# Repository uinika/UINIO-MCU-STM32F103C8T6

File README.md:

# UINIO-MCU-STM32F103C8T6 核心板

[**UINIO-MCU-STM32F103C8T6**](https://gitee.com/uinika/UINIO-MCU-STM32F103C8T6) 是一款基于 [**意法半导体**](https://www.st.com/zh/microcontrollers-microprocessors/stm32-32-bit-arm-cortex-mcus.html) **LQFP48** 封装的 **STM3232F103C8T6** 微控制器的核心板电路设计，该微控制器基于 **ARM Cortex-M3** 内核架构，主频可以达到 `72MHz`，片上载有 `64KB` 容量的 Flash 存储器和 `20Kbytes` 的 SRAM 存储器，并且拥有 3 组 **USART** 和 2 组 **I²C** 接口，以及 2 组 **SPI** 接口与 `USB2.0` 全速控制器、12 位分辨率的 `ADC/DAC` 转换器，整体上属于外设资源比较完善的高性价比主控芯片产品。

## 设计概要

1. 引出了意法半导体 **STM32F103C8T6** 型微控制器上面的全部 GPIO 引脚资源；
2. 单独提供有四线制的 **SWD** 下载接口，便于快速与 [UINIO-DAP-Link](http://uinio.com/Project/UINIO-DAP-Link) 建立连接；
3. 分别使用了 `8MHz` 与 `32.768KHz` 两枚贴片晶振作为系统外部时钟与实时时钟；
4. 板载 **BOOT0** 和 **BOOT1** 两枚启动配置按钮，以及一枚 **NRST** 复位按钮；
5. 模拟电源引脚 `VDDA` 使用了对 `100Mhz` 高频杂散信号存在 `1KΩ` 阻抗的**磁珠**进行单点接地；

## 启动配置

**UINIO-MCU-STM32F103C8T6** 通过板载的 `BOOT0` 和 `BOOT1` 两枚按钮来配置启动方式，默认情况下是从片上的 Flash 闪存进行启动，具体的配置信息可以参见下表：

| BOOT0 | BOOT1 | 启动方式                 |
| :---: | :---: | :----------------------- |
|  `0`  |  `X`  | 片上 Flash 闪存          |
|  `1`  |  `0`  | 系统存储器/ISP           |
|  `1`  |  `1`  | 片上 SRAM 静态随机存储器 |

## 参考技术文档

[UinIO.com 电子技术实验室](http://uinio.com/) 为 UINIO-MCU-STM32F103C8T6 开源项目提供了如下一系列技术参考资料：

1. [《意法半导体 STM32F103C8T6 标准库典型实例》](http://uinio.com/Embedded/STM32F103/)
2. [《ARM 调试工具 UINIO-DAP-Link 应用详解》](http://uinio.com/Project/UINIO-DAP-Link/)
3. [《BOM 交互式物料清单与 PCB 布线在线预览》](http://uinio.com/archives/BOM/UINIO-MCU-STM32F103C8T6.html)

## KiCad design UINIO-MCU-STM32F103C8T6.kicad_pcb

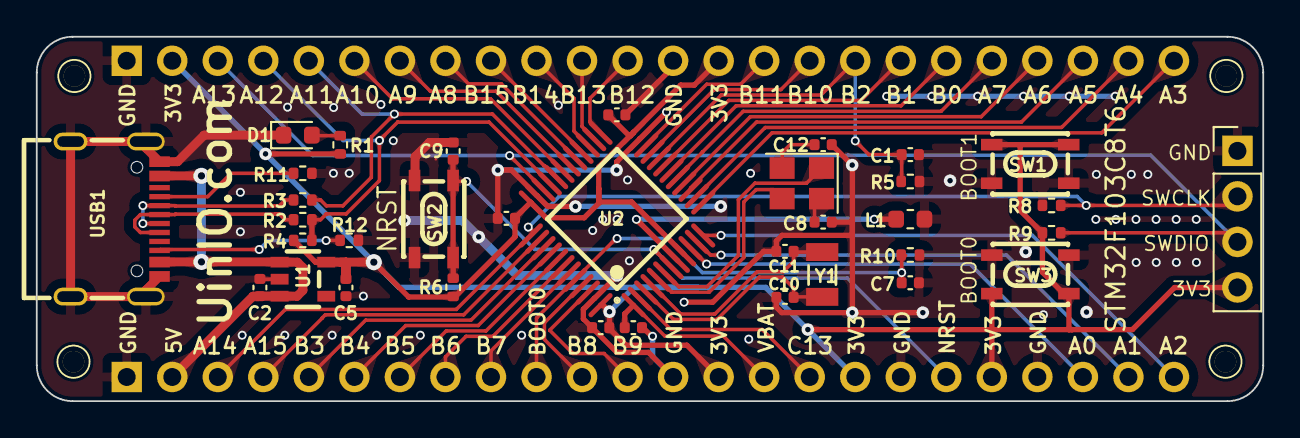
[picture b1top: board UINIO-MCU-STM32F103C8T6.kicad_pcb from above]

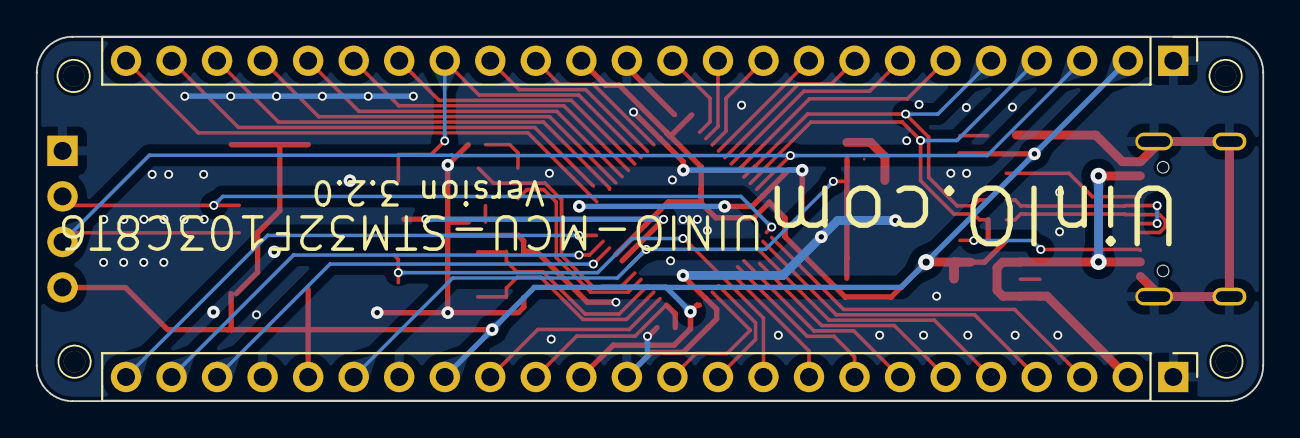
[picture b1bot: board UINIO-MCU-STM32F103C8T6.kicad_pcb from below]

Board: 2 copper layers, 68.4 x 20.3 mm, 41 parts (2 on the bottom side), 51 nets.

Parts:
C1, C3, C4, C6, C7, C9, C13: 0.1uF; C_0402_1005Metric
C2, C5: 1uF; C_0402_1005Metric
C8, C12: 22pF; C_0402_1005Metric
C10, C11: 10pF; C_0402_1005Metric
D1: LED_Red; LED_0603_1608Metric
HOLE**: Hole-1mm
HOLE**#2, HOLE**#3, HOLE**#4: Hole-1mm
J1, J2: Conn_01x24_Pin; PinHeader_1x24_P2.54mm_Vertical
J3: Conn_01x04_Pin; PinHeader_1x04_P2.54mm_Vertical
L1: 1KΩ 100Mhz; L_0603_1608Metric
R1: 2K; R_0402_1005Metric
R2, R3: 50R; R_0402_1005Metric
R4: 1.5K; R_0402_1005Metric
R5, R6, R8, R9, R10: 10K; R_0402_1005Metric
R11, R12: 5.1K; R_0402_1005Metric
SW1: BOOT1; KEY-SMD_4P-L4.2-W3.4-P2.15-LS4.7
SW2: NRST; KEY-SMD_4P-L4.2-W3.4-P2.15-LS4.7
SW3: BOOT0; KEY-SMD_4P-L4.2-W3.4-P2.15-LS4.7
U1: ME6211C33M5G-N; SOT-23-5_L3.0-W1.7-P0.95-LS2.8-BR
U2: STM32F103C8T6; TQFP-48_L7.0-W7.0-P0.50-LS9.0-BL
USB1: USB_Type_C_16Pin; USB-C-SMD_TYPEC-304J-BCP16
Y1: 32.768KHz; CRYSTAL-FC135-32.768
Y2: 8MHz; Crystal_SMD_3225-4Pin_3.2x2.5mm

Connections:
/BOOT0: C7.2, J2.10, R10.1, U2.44 (BOOT0)
/NRST: C9.1, J2.19, R6.2, SW2.1, SW2.2, U2.7 (NRST)
/PA0: J2.22, U2.10 (PA0_WAKEUP)
/PA1: J2.23, U2.11 (PA1)
/PA2: J2.24, U2.12 (PA2)
/PA3: J1.24, U2.13 (PA3)
/PA4: J1.23, U2.14 (PA4)
/PA5: J1.22, U2.15 (PA5)
/PA6: J1.21, U2.16 (PA6)
/PA7: J1.20, U2.17 (PA7)
/PA8: J1.8, U2.29 (PA8)
/PA9: J1.7, U2.30 (PA9)
/PA10: J1.6, U2.31 (PA10)
/PA13/SWDIO: J1.3, J3.3, R9.1, U2.34 (PA13)
/PA14/SWCLK: J2.3, J3.2, R8.2, U2.37 (PA14)
/PA15: J2.4, U2.38 (PA15)
/PB0: J1.19, U2.18 (PB0)
/PB1: J1.18, U2.19 (PB1)
/PB2/BOOT1: C1.2, J1.17, R5.1, U2.20 (PB2)
/PB3: J2.5, U2.39 (PB3)
/PB4: J2.6, U2.40 (PB4)
/PB5: J2.7, U2.41 (PB5)
/PB6: J2.8, U2.42 (PB6)
/PB7: J2.9, U2.43 (PB7)
/PB8: J2.11, U2.45 (PB8)
/PB9: J2.12, U2.46 (PB9)
/PB10: J1.16, U2.21 (PB10)
/PB11: J1.15, U2.22 (PB11)
/PB12: J1.12, U2.25 (PB12)
/PB13: J1.11, U2.26 (PB13)
/PB14: J1.10, U2.27 (PB14)
/PB15: J1.9, U2.28 (PB15)
/PC13: J2.16, U2.2 (PC13_TAMPER_RTC)
/USB_Data+: R2.1, USB1.A6 (DP1), USB1.B6 (DP2)
/USB_Data-: R3.1, USB1.A7 (DN1), USB1.B7 (DN2)
/USB_PA+: J1.4, R2.2, R4.2, U2.33 (PA12)
/USB_PA-: J1.5, R3.2, U2.32 (PA11)
/VBAT: C13.2, J2.15, U2.1 (VBAT)
/VDD_3.3V: C3.2, C4.2, C5.2, C6.2, J1.2, J1.14, J2.14, J2.17, J2.20, J3.4, R1.2, R4.1, R6.1, R9.2, SW1.3, SW1.4, SW3.3, SW3.4, U1.5 (Vout), U2.9 (VDDA), U2.24 (VDD_1), U2.36 (VDD_2), U2.48 (VDD_3)
/VDD_5V: C2.2, J2.2, U1.1 (Vin), U1.3 (CE), USB1.A4B9 (VBUS), USB1.B4A9 (VBUS)
GND: C1.1, C2.1, C3.1, C4.1, C5.1, C6.1, C7.1, C8.1, C9.2, C10.1, C11.1, C12.1, C13.1, D1.1 (K), J1.1, J1.13, J2.1, J2.13, J2.18, J2.21, J3.1, L1.1, R5.2, R8.1, R10.2, R11.2, R12.2, SW1.1, SW1.2, SW2.3, SW2.4, SW3.1, SW3.2, U1.2 (Vss), U2.23 (VSS_1), U2.35 (VSS_2), U2.47 (VSS_3), USB1.13 (GND), USB1.14 (GND), USB1.15 (GND), USB1.16 (GND), USB1.A1B12 (GND), USB1.B1A12 (GND)
unnamed: C8.2, Y2.4
unnamed: C12.2, Y2.2
unnamed: D1.2 (A), R1.1
unnamed: C10.2, U2.3 (PC14_OSC32_IN), Y1.2 (GND)
unnamed: C11.2, U2.4 (PC15_OSC32_OUT), Y1.1
unnamed: U2.5 (PD0_OSC_IN), Y2.3
unnamed: U2.6 (PD1_OSC_OUT), Y2.1
unnamed: L1.2, U2.8 (VSSA)
unnamed: R11.1, USB1.A5 (CC1)
unnamed: R12.1, USB1.B5 (CC2)

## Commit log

2024-02-04 Initialization project.
2024-02-04 Add reference documents.
2024-02-05 Complete wiring.
2024-02-05 Finish PCB layout.
2024-02-06 Release UINIO-MCU-STM32F103C8T6 version 3.0.0.
2024-04-12 Release UINIO-MCU-STM32F103C8T6 version 3.1.0.
2024-04-13 Release UINIO-MCU-STM32F103C8T6 version 3.2.0.
